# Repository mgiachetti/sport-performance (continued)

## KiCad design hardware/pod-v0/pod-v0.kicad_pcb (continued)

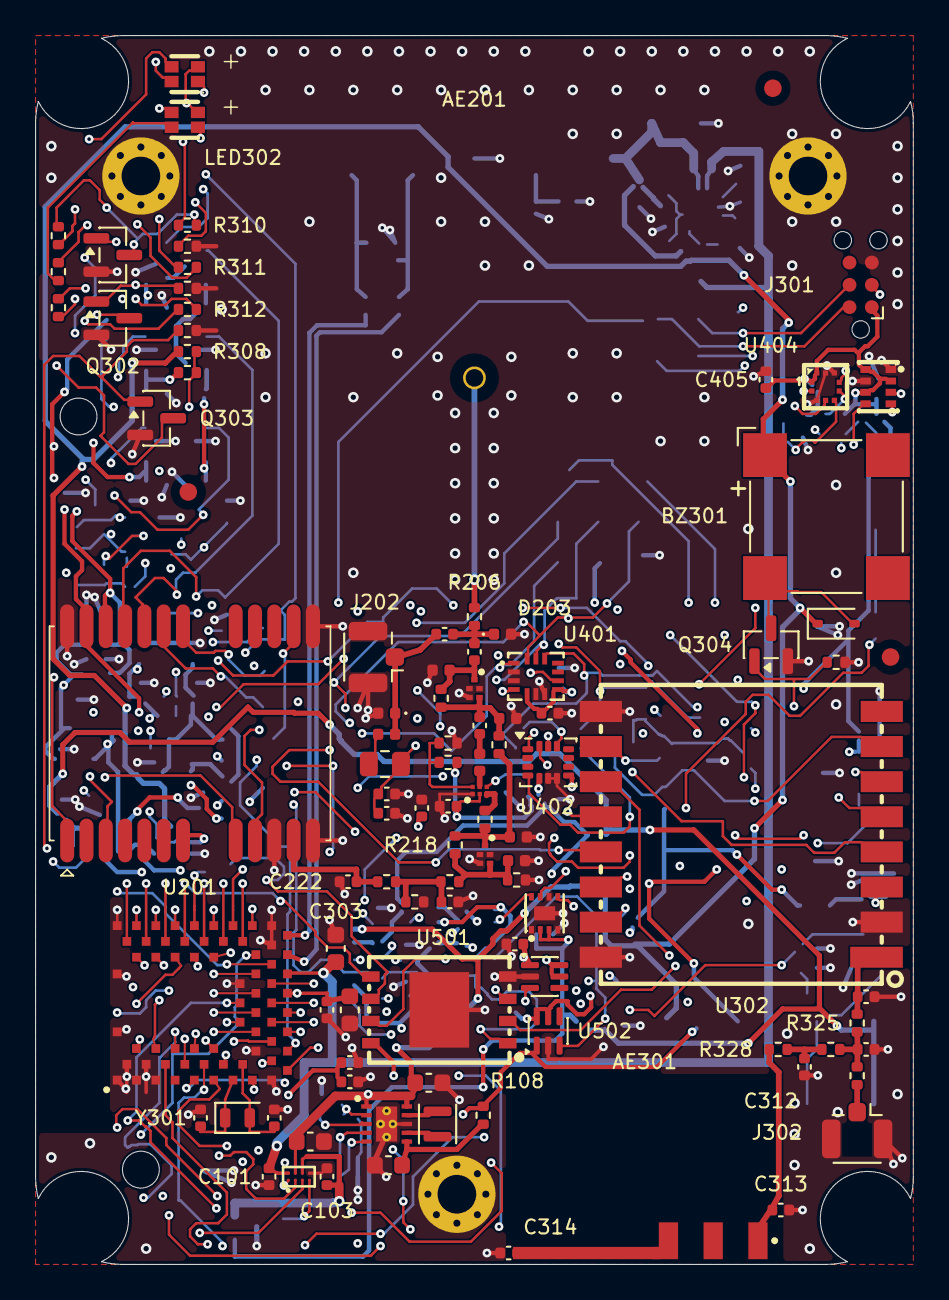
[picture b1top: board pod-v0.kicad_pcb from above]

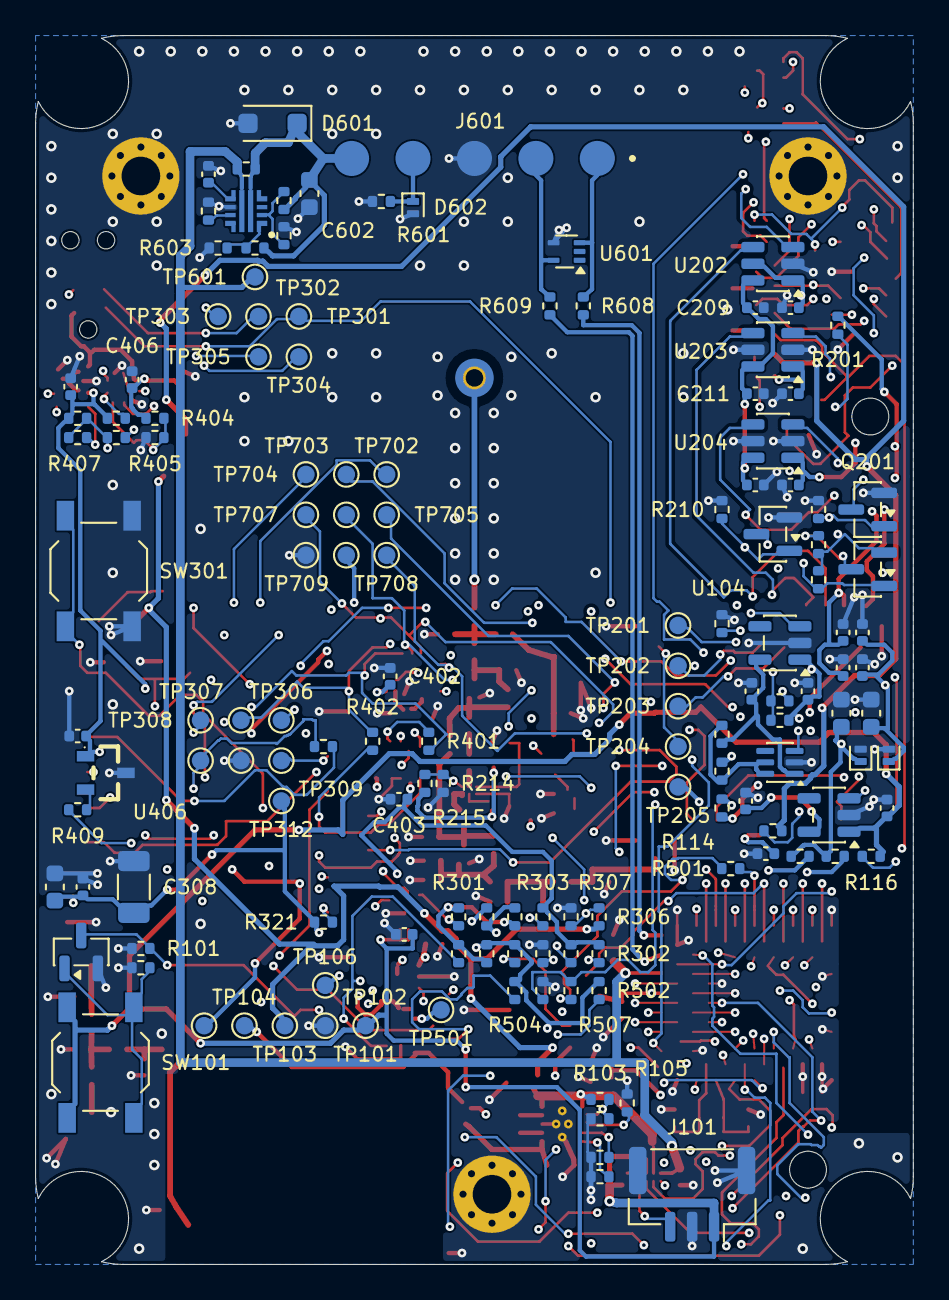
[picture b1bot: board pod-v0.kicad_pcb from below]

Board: 6 copper layers, 50.0 x 70.0 mm, 249 parts (144 on the bottom side), 139 nets.

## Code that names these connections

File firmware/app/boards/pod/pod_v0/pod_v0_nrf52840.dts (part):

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	zephyr,user {
		gnss-uart = <&uart0>;
		/* EN of the 3,2 V LDO of the GNSS (active discharge): the GNSS power cut. */
		gnss-en-gpios = <&gpio1 13 GPIO_ACTIVE_HIGH>;	/* GNSS_EN, pad 62 */
		/* NPN/NMOS open drain to RESET_N: high here = module in reset (≥ 100 ms). */
		gnss-reset-gpios = <&gpio0 3 GPIO_ACTIVE_HIGH>;	/* GNSS_RST, pad 19 */
		/* WAKEUP (3,0–3,6 V high): ≥ 10 ms pulse out of backup, input otherwise. */
		gnss-wakeup-gpios = <&gpio0 9 GPIO_ACTIVE_HIGH>;	/* GNSS_WAKEUP, pad 25 (NFC1) */
		/* 1PPS: GPIOTE → PPI → TIMER capture (app/src/time_base.c). */
		gnss-pps-gpios = <&gpio1 10 (GPIO_ACTIVE_HIGH | GPIO_PULL_UP)>;	/* pad 53 */
		/* DRV5032FA (or FB) push-pull through a series resistor: low = pod in the vest. */
		hall-gpios = <&gpio0 10 GPIO_ACTIVE_LOW>;	/* HALL_INT, pad 26 (NFC2) */
		/* BQ25180 /INT, open drain, 128 µs pulse. */
		chg-int-gpios = <&gpio1 11 (GPIO_ACTIVE_LOW | GPIO_PULL_UP)>;	/* pad 54 */
		/* MAX17048 /ALRT, open drain. */
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		/* Bench button to GND. */
		button-gpios = <&gpio1 15 (GPIO_ACTIVE_LOW | GPIO_PULL_UP)>;	/* pad 64 */
		/* ON of the TPS22919 load switch of the Ra-01SH (U303). */
		lora-en-gpios = <&gpio1 1 GPIO_ACTIVE_HIGH>;	/* LORA_EN, pad 57 */
		/* EN of the NAND load switch (U502, not mounted) by 0 Ω, 100 kΩ pull-down. */
		nand-en-gpios = <&gpio1 3 GPIO_ACTIVE_HIGH>;	/* NAND_EN, pad 59 */
		/*
		 * UWB: the DWM3000 left the v0 on 15/11/2026; these pins end on test
		 * points for a bench DWM3000EVB (B-911). Without the EVB they float:
		 * if the firmware ever reads UWB_IRQ, give it GPIO_PULL_DOWN here (and
		 * leave UWB_RST and UWB_WAKEUP as disconnected inputs).
		 */
		uwb-irq-gpios = <&gpio1 2 GPIO_ACTIVE_HIGH>;	/* pad 58 */
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
/*
 * UICR, written at the first programming (production step, B-909): NFC pads
 * P0.09/P0.10 as GPIO (GNSS WAKEUP and Hall) and P0.18 as nRESET.
 */
&uicr {
	nfct-pins-as-gpios;
	gpio-as-nreset;
};

&nfct {
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	baro: bmp581@47 {
		compatible = "bosch,bmp581";
		reg = <0x47>;
		int-gpios = <&gpio1 12 (GPIO_ACTIVE_LOW | GPIO_PULL_UP)>;	/* BARO_INT, pad 61 */
	};
};

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	pinctrl-0 = <&spi1_default>;
	pinctrl-1 = <&spi1_sleep>;
	pinctrl-names = "default", "sleep";
	cs-gpios = <&gpio1 9 GPIO_ACTIVE_LOW>,	/* IMU_CS, pad 52 */
		   <&gpio0 27 GPIO_ACTIVE_LOW>;	/* UWB_CS, pad 8: test point (bench DWM3000EVB) */

	/*
	 * LSM6DSV32X (WHO_AM_I 0x70): driven by the lsm6dsv16x driver of NCS 3.4.1
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		reg = <0>;
		spi-max-frequency = <8000000>;
		accel-range = <16>;
		int1-gpios = <&gpio1 4 GPIO_ACTIVE_HIGH>;	/* IMU_INT1, pad 60: motion wake-up */
		int2-gpios = <&gpio1 6 GPIO_ACTIVE_HIGH>;	/* IMU_INT2, pad 49 */
	};
};

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	pinctrl-0 = <&spi2_default>;
	pinctrl-1 = <&spi2_sleep>;
	pinctrl-names = "default", "sleep";
	cs-gpios = <&gpio0 16 GPIO_ACTIVE_LOW>;	/* LORA_NSS, pad 34 */

	/*
	 * Ai-Thinker Ra-01SH: plain crystal, no TCXO (no dio3-tcxo-voltage). Its RF
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		compatible = "semtech,sx1262";
		reg = <0>;
		spi-max-frequency = <8000000>;
		reset-gpios = <&gpio0 31 GPIO_ACTIVE_LOW>;	/* LORA_NRST, pad 12 */
		busy-gpios = <&gpio0 2 GPIO_ACTIVE_HIGH>;	/* LORA_BUSY, pad 15 */
		dio1-gpios = <&gpio0 29 GPIO_ACTIVE_HIGH>;	/* LORA_DIO1, pad 10 */
		rx-enable-gpios = <&gpio0 30 GPIO_ACTIVE_HIGH>;	/* LORA_RXEN, pad 11 */
		dio2-tx-enable;
	};
};
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	pinctrl-0 = <&spi3_default>;
	pinctrl-1 = <&spi3_sleep>;
	pinctrl-names = "default", "sleep";
	cs-gpios = <&gpio0 17 GPIO_ACTIVE_LOW>;	/* NAND_CS, pad 35 */
	/* Errata 198: the SPIM3 buffers live in their own RAM block (app/src/log_nand.c). */

	nand: w25n02kv@0 {
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
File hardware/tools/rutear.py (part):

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    # had it) both switch nodes had to cross VOUT: it goes to the east side, standing, so pad 1 faces LX1 (pin 9)
    # and pad 2 faces LX2 (pin 7), 0.65 mm from the pins (courtyard against courtyard).
    "L101": (22.9, 62.0, 270, "inductor del buck-boost al lado de LX1/LX2 (hoja del TPS63900, layout)"),
    "C105": (22.4, 59.65, 0, "capacitor de entrada pegado a VIN (pin 10), con el SYS hacia el pin"),
    "C106": (20.1, 64.35, 180, "capacitor de salida pegado a VOUT (pin 6) y al pad expuesto"),
    # BQ25180 (DSBGA, 0.4 mm): the four balls of each row escape straight out of their row. SYS (B2) leaves to the
    # north, so its capacitor goes north; BAT (C2) and GND (D2) leave to the north and east, so C103 turns with
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    "C102": (15.65, 63.0, 0, "capacitor de SYS del cargador al norte, donde sale la bola B2"),
    "C103": (16.6, 65.0, 90, "capacitor de BAT del cargador girado: su pad de GND frente a la bola D2"),
    # TPS63900: the pull-downs of CFG1 to CFG3 sat in a column on the bottom side right under the only free copper of
    # L1 next to the pins (walled in by SYS, C102, BAT and the pins): no via fitted between their pads (0.48 mm), and
    # two of the three nets were left open run after run (26/11/2026). R105 (CFG1) goes west, standing, next to the
    # via that CFG1 takes anyway; its row is left for the vias of CFG2 and CFG3 (``pads_encerrados``).
    "R105": (16.3, 60.8, 90, BB_CFG),
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    "R214": (26.78, 42.6, 270, "pull-down del control 2 del LNA 0,18 mm al este: la vía quedaba a 0,02 mm del pad 1"),
    "R215": (27.82, 42.6, 270, "pull-up del control 2 del LNA 0,12 mm al este, junto con R214"),
    "C403": (29.3, 43.5, 0, "100 nF del ICM-42688-P 0,1 mm al este, para que entren R214 y R215 sin que se toquen"),
    # MAX17048: its BAT pins (2 and 3) are the middle two of the bottom row and C309 (the input capacitor of the
    # LoRa load switch) sat 0.29 mm below them, so they had no way out. C309 goes to the left of the load switch,
    # right above its VREG_LORA pin (pin 1).
    "C309": (27.3, 51.75, 180, "capacitor de VREG_LORA al lado del pin 1 de U303: dejaba encerrados los pines BAT del MAX17048"),
    # BMD-340: its second top row escapes to a row of vias at y = 48.3; R501 (the 22 ohm of NAND_SCK, bottom side,
    # under pad 37) sat on that row.
    "R501": (10.4, 47.45, 0, "22 ohm de NAND_SCK corrido 1,35 mm al este: pisaba la fila de vías del escape del BMD-340"),
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    # BMD-340 (x 15.1 and 15.85: no via in its pads since 27/11/2026).
    r.track("VBUS", "B", PWR, [(16.9, 58.5), (16.9, 53.9), (16.4, 53.4)])
    r.via("VBUS", (16.4, 53.4), VIA_PWR)
    # the pin only senses VBUS: 0.2 mm leaves room for the USB via and for the via of pad 25 (GNSS_WAKEUP) below
    r.track("VBUS", "F", 0.2, [(14.35, 53.4), (16.4, 53.4)])  # 0.05 mm north of the pad's centre
    r.track("VBUS", "F", PWR, [(16.4, 53.4), (17.05, 52.75)])
    # And on to the charger: L4 down to a via west of the BQ25180, L1 to its capacitor (C101) and ball A2.
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    # charge current. L4 along the bottom edge and up east of the buck-boost's resistors, one hop on L1 over the
    # VBUS run (y 58.5) east of the NAND, L4 again to a via east of U102, and L1 to the pins (from below, where
    # C309 used to be). C104 (its 1 uF) on L4 under U102. Along the edge at y 69.55 (0.325 mm from it), not 69.2:
    # with BAT above and below, the GND pin of J101 had no room for its via and was left on an island (26/11/2026).
    # It turns east at y 61.2, not 60.4, to leave room for the SYS via of R103 (pads_encerrados).
    r.track("BAT", "B", 0.25, [(11.35, 68.6), (11.35, 69.55), (18.65, 69.55), (19.0, 69.2), (19.0, 61.2), (19.7, 60.5),
                               (20.3, 59.9), (25.5, 59.9)])
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    r.track("BAT", "B", 0.25, [(30.0, 52.0), (28.52, 52.0), "C104.1"])
    r.track("BAT", "F", 0.2, [(30.35, 51.5), (28.75, 51.5), "U102.2"])
    r.track("BAT", "F", 0.2, [(29.25, 51.5), "U102.3"])
    # SYS from the charger's capacitor to the buck-boost: VIN (pin 10) through its input capacitor (C105) and EN
    # (pin 1).
    r.track("SYS", "F", PWR, ["C102.1", (14.875, 62.6), (17.075, 60.4), (21.4, 60.4)])
    r.track("SYS", "F", 0.3, [(21.15, 60.4), "U103.10"])
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    # GND: pin 8 to the exposed pad; the output capacitor to the exposed pad on L1.
    r.track("GND", "F", 0.2, ["U103.8", (20.6, 62.0)])
    r.track("GND", "F", 0.3, ["C106.2", (19.35, 64.0), (19.8, 63.0)])
    # VOUT: pin 6 -> output capacitor -> under the inductor -> R108 (0 ohm to VREG).
    r.track("VREG_BB", "F", 0.3, ["U103.6", (21.15, 63.45), "C106.1"])
    r.track("VREG_BB", "F", 0.3, [(21.15, 63.45), (24.0, 63.45), (25.3, 62.15), "R108.1"])
    # VREG_LORA: C309 (moved next to it) to pin 1 of the LoRa load switch.
    r.track("VREG_LORA", "F", 0.3, ["C309.1", (27.9, 52.4), "U303.1"])
    # LORA_EN (pin 3) is boxed in by the NAND's pads, 0.25 mm to the west: out to the south to a via.
    r.track("LORA_EN", "F", 0.15, ["U303.3", (27.9, 54.5), (27.9, 55.0)])
    r.via("LORA_EN", (27.9, 55.0))

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    r.track("SYS", "B", 0.25, ["R103.2", (18.95, 60.3)])
    r.via("SYS", (18.95, 60.3))
    r.track("SYS", "F", 0.25, [(18.95, 60.3), (18.95, 60.4)])
    # Battery connector (J101): its GND pin between BAT and the cell sense of the MAX17048, a via just south of it.
    r.track("GND", "B", 0.3, ["J101.2", (12.6, 68.95)])
    r.via("GND", (12.6, 68.95))
    # Charger (U101): D2 (GND) and C103's GND pad sit inside the BAT loop of L1, and their piece of the fill gets out
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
